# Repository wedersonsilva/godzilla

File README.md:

# Godzilla robot [en]

An autonomous sumo fight robot called Godzilla!

Created by Alisson Ricardo, Godzilla won battles into local sumo robot fights.

It was donated to LabPRO and now is being updated by Celson Nakamura, Paulo Nascimento and me (Wederson Silva)

# Robô Godzilla [br]

Um robô autônomo de batalha sumô chamado Godzilla!

Foi criado por Alisson Ricardo, Godzilla ganhou batalhas nos torneios locais de batalha sumô.

Foi doado ao LabPRO e agora está sendo atualizado por Celson Nakamura, Paulo Nascimento por mim (Wederson Silva)

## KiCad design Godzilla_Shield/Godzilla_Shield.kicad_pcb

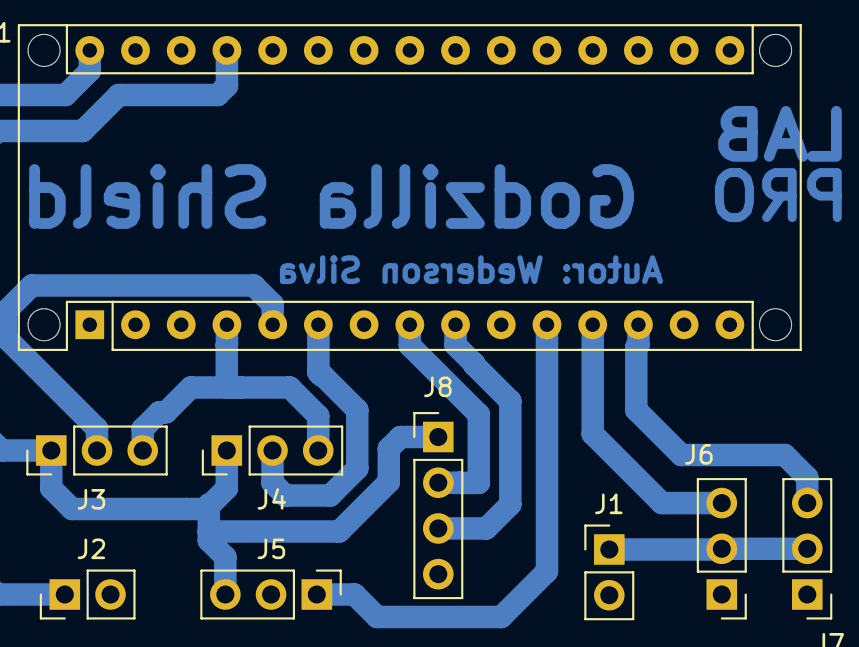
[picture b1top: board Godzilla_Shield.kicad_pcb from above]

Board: 2 copper layers, 9 parts (0 on the bottom side), 11 nets.

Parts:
A1: Arduino_Nano_v3.x; Arduino_Nano_WithMountingHoles
J1: 6V; Pin_Header_Straight_1x02_Pitch2.54mm
J2: 12V; Pin_Header_Straight_1x02_Pitch2.54mm
J3: Linha_Esq; Pin_Header_Straight_1x03_Pitch2.54mm
J4: Linha_Dir; Pin_Header_Straight_1x03_Pitch2.54mm
J5: Obstaculo; Pin_Header_Straight_1x03_Pitch2.54mm
J6: Motor_Esq; Pin_Header_Straight_1x03_Pitch2.54mm
J7: Motor_Dir; Pin_Header_Straight_1x03_Pitch2.54mm
J8: Ultrassom; Pin_Header_Straight_1x04_Pitch2.54mm

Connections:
/5V: A1.27, J3.1, J4.1, J5.3, J8.1
/6V: J1.1, J6.2, J7.2
/ECHO: A1.9, J8.3
/GND: A1.4, A1.29, J1.2, J2.2, J3.3, J4.3, J5.2, J6.1, J7.1, J8.4
/TRIG: A1.8, J8.2
unnamed: A1.5, J3.2
unnamed: A1.6, J4.2
unnamed: A1.11, J5.1
unnamed: A1.12, J6.3
unnamed: A1.13, J7.3
unnamed: A1.30, J2.1

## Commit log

2018-11-15 Adiciona o esquemático e PCB
2018-11-15 Adiciona a versão 2 da placa
2018-11-16 Adiciona o .gitignore
